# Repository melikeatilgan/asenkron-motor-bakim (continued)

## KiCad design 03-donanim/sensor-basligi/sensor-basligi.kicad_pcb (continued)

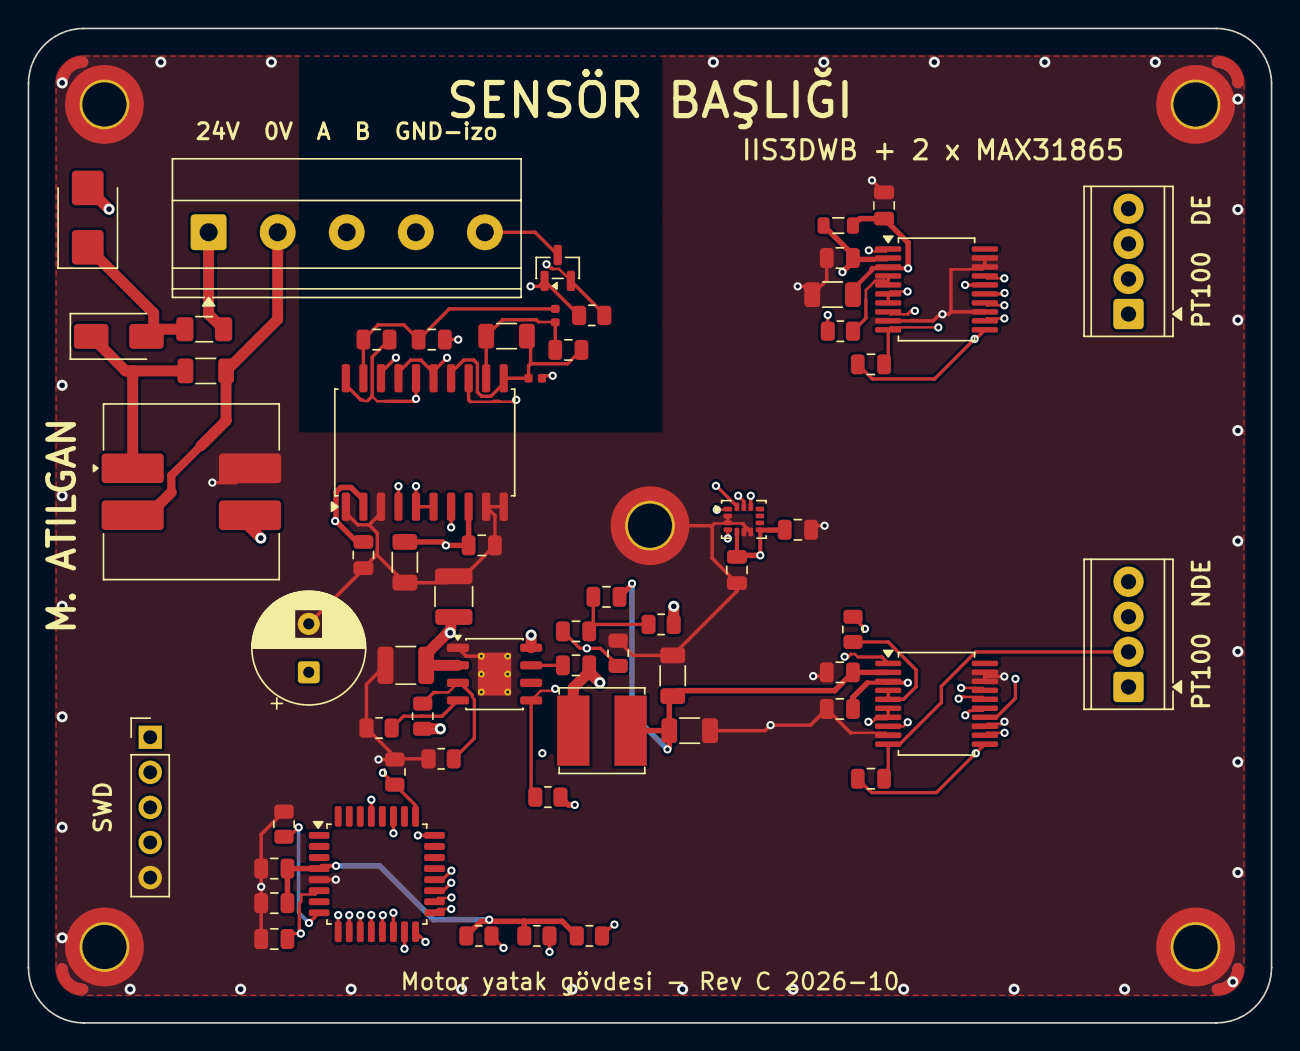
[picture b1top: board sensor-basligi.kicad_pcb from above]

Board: 4 copper layers, 90.0 x 72.0 mm, 66 parts (0 on the bottom side), 50 nets.

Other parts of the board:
MH1, MH2, MH3, MH4, MH5: MountingHole_3.2mm_M3_ISO7380_Pad_TopBottom

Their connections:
GND: MH1.1, MH2.1, MH3.1, MH4.1, MH5.1; also elsewhere on the board

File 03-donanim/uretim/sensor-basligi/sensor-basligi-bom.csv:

"Refs","Value","Footprint","Qty","DNP"
"C1","470n 100V","Capacitor_SMD:C_1206_3216Metric","1",""
"C2","2u2 100V","Capacitor_SMD:C_1210_3225Metric","1",""
"C3","2n2 50V","Capacitor_SMD:C_0805_2012Metric","1",""
"C4","22u 10V","Capacitor_SMD:C_1206_3216Metric","1",""
"C5","22u 10V","Capacitor_SMD:C_1206_3216Metric","1",""
"C6","3n3","Capacitor_SMD:C_0805_2012Metric","1",""
"C7","330p","Capacitor_SMD:C_0805_2012Metric","1",""
"C8","2u2 100V","Capacitor_SMD:C_1210_3225Metric","1",""
"C9","47u 63V","Capacitor_THT:CP_Radial_D8.0mm_P3.50mm","1",""
"C10","10u","Capacitor_SMD:C_1206_3216Metric","1",""
"C20","100n","Capacitor_SMD:C_0805_2012Metric","1",""
"C21","1u","Capacitor_SMD:C_0805_2012Metric","1",""
"C22","100n","Capacitor_SMD:C_0805_2012Metric","1",""
"C30","100n","Capacitor_SMD:C_0805_2012Metric","1",""
"C31","1u","Capacitor_SMD:C_0805_2012Metric","1",""
"C40","100n","Capacitor_SMD:C_0805_2012Metric","1",""
"C41","100n","Capacitor_SMD:C_0805_2012Metric","1",""
"C42","100n","Capacitor_SMD:C_0805_2012Metric","1",""
"C43","100n","Capacitor_SMD:C_0805_2012Metric","1",""
"C44","100n","Capacitor_SMD:C_0805_2012Metric","1",""
"C45","100n","Capacitor_SMD:C_0805_2012Metric","1",""
"C50","100n","Capacitor_SMD:C_0805_2012Metric","1",""
"C51","10u","Capacitor_SMD:C_1206_3216Metric","1",""
"C52","100n","Capacitor_SMD:C_0805_2012Metric","1",""
"C53","100n","Capacitor_SMD:C_0805_2012Metric","1",""
"C54","10u","Capacitor_SMD:C_1206_3216Metric","1",""
"C55","100n","Capacitor_SMD:C_0805_2012Metric","1",""
"C56","10n","Capacitor_SMD:C_0805_2012Metric","1",""
"D1","SMBJ33CA","Diode_SMD:D_SMB","1",""
"D2","SS110","Diode_SMD:D_SMA","1",""
"D10","SM712","Package_TO_SOT_SMD:SOT-23","1",""
"F1","500mA T 63V 0468.500NR","Fuse:Fuse_1206_3216Metric","1",""
"FB1","600R 100MHz","Inductor_SMD:L_0805_2012Metric","1",""
"FB2","BLM15HD182SN1D","Inductor_SMD:L_0402_1005Metric","1",""
"FB3","BLM15HD182SN1D","Inductor_SMD:L_0402_1005Metric","1",""
"J1","Ana karta kablo","TerminalBlock_Phoenix:TerminalBlock_Phoenix_MKDS-1,5-5_1x05_P5.00mm_Horizontal","1",""
"J2","PT100 4 telli","TerminalBlock_Phoenix:TerminalBlock_Phoenix_MPT-0,5-4-2.54_1x04_P2.54mm_Horizontal","1",""
"J3","PT100 4 telli","TerminalBlock_Phoenix:TerminalBlock_Phoenix_MPT-0,5-4-2.54_1x04_P2.54mm_Horizontal","1",""
"J4","SWD","Connector_PinHeader_2.54mm:PinHeader_1x05_P2.54mm_Vertical","1",""
"L1","SRF1260-101M","Inductor_SMD:L_CommonModeChoke_Bourns_SRF1260","1",""
"L2","33uH SRN6045TA-330M","Inductor_SMD:L_Bourns_SRN6045TA","1",""
"R1","499k","Resistor_SMD:R_0805_2012Metric","1",""
"R2","48k7","Resistor_SMD:R_0805_2012Metric","1",""
"R3","86k6","Resistor_SMD:R_0805_2012Metric","1",""
"R4","49k9","Resistor_SMD:R_0805_2012Metric","1",""
"R5","27k4","Resistor_SMD:R_0805_2012Metric","1",""
"R6","143k","Resistor_SMD:R_0805_2012Metric","1",""
"R10","10k","Resistor_SMD:R_0805_2012Metric","1",""
"R11","10k","Resistor_SMD:R_0805_2012Metric","1",""
"R12","10k","Resistor_SMD:R_0805_2012Metric","1",""
"R13","10k","Resistor_SMD:R_0805_2012Metric","1",""
"R14","10k","Resistor_SMD:R_0805_2012Metric","1",""
"R20","400R 0.1% 10ppm","Resistor_SMD:R_0805_2012Metric","1",""
"R21","400R 0.1% 10ppm","Resistor_SMD:R_0805_2012Metric","1",""
"R30","120R","Resistor_SMD:R_0805_2012Metric","1",""
"U1","LM5164DDA","Package_SO:HSOP-8-1EP_3.9x4.9mm_P1.27mm_EP2.41x3.1mm_ThermalVias","1",""
"U3","STM32G071KBTxN","Package_QFP:LQFP-32_7x7mm_P0.8mm","1",""
"U4","IIS3DWB","Package_LGA:LGA-14_3x2.5mm_P0.5mm_LayoutBorder3x4y","1",""
"U5","MAX31865AAP+","Package_SO:SSOP-20_5.3x7.2mm_P0.65mm","1",""
"U6","MAX31865AAP+","Package_SO:SSOP-20_5.3x7.2mm_P0.65mm","1",""
"U7","ADM2582E","Package_SO:SOIC-20W_7.5x12.8mm_P1.27mm","1",""

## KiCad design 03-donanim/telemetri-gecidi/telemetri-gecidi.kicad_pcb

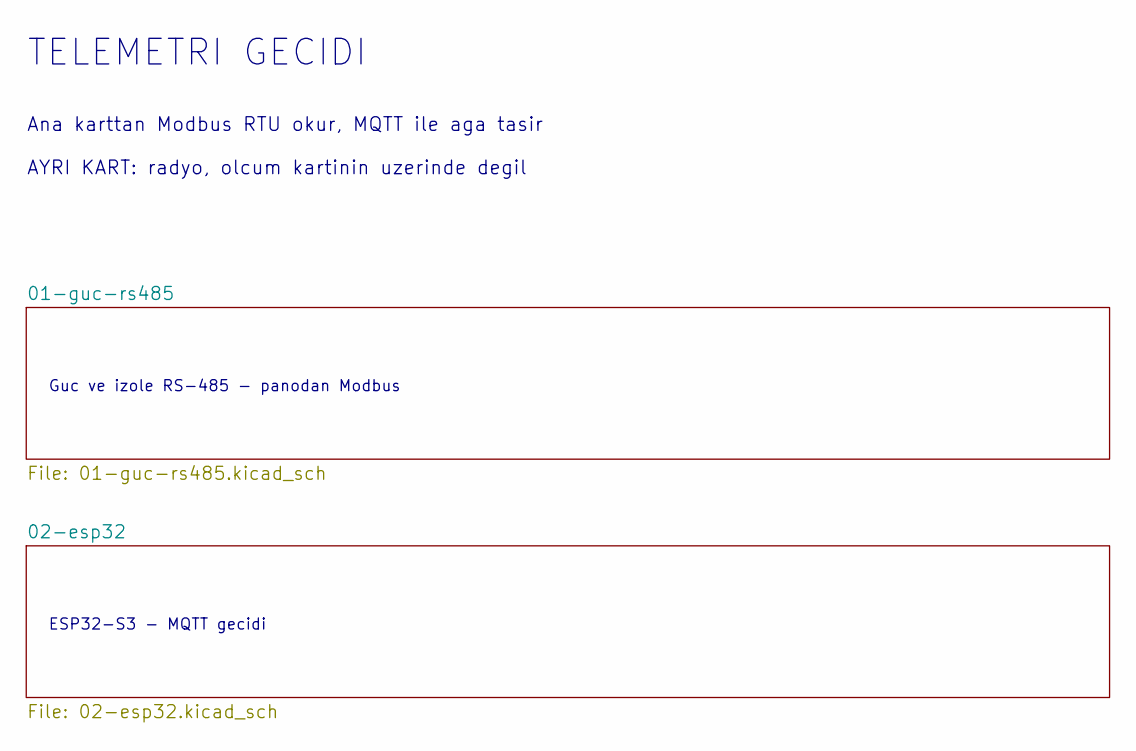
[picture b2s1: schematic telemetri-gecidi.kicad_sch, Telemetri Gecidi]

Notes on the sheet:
AYRI KART: radyo, olcum kartinin uzerinde degil
Ana karttan Modbus RTU okur, MQTT ile aga tasir
ESP32-S3 - MQTT gecidi
Guc ve izole RS-485 - panodan Modbus
TELEMETRI GECIDI

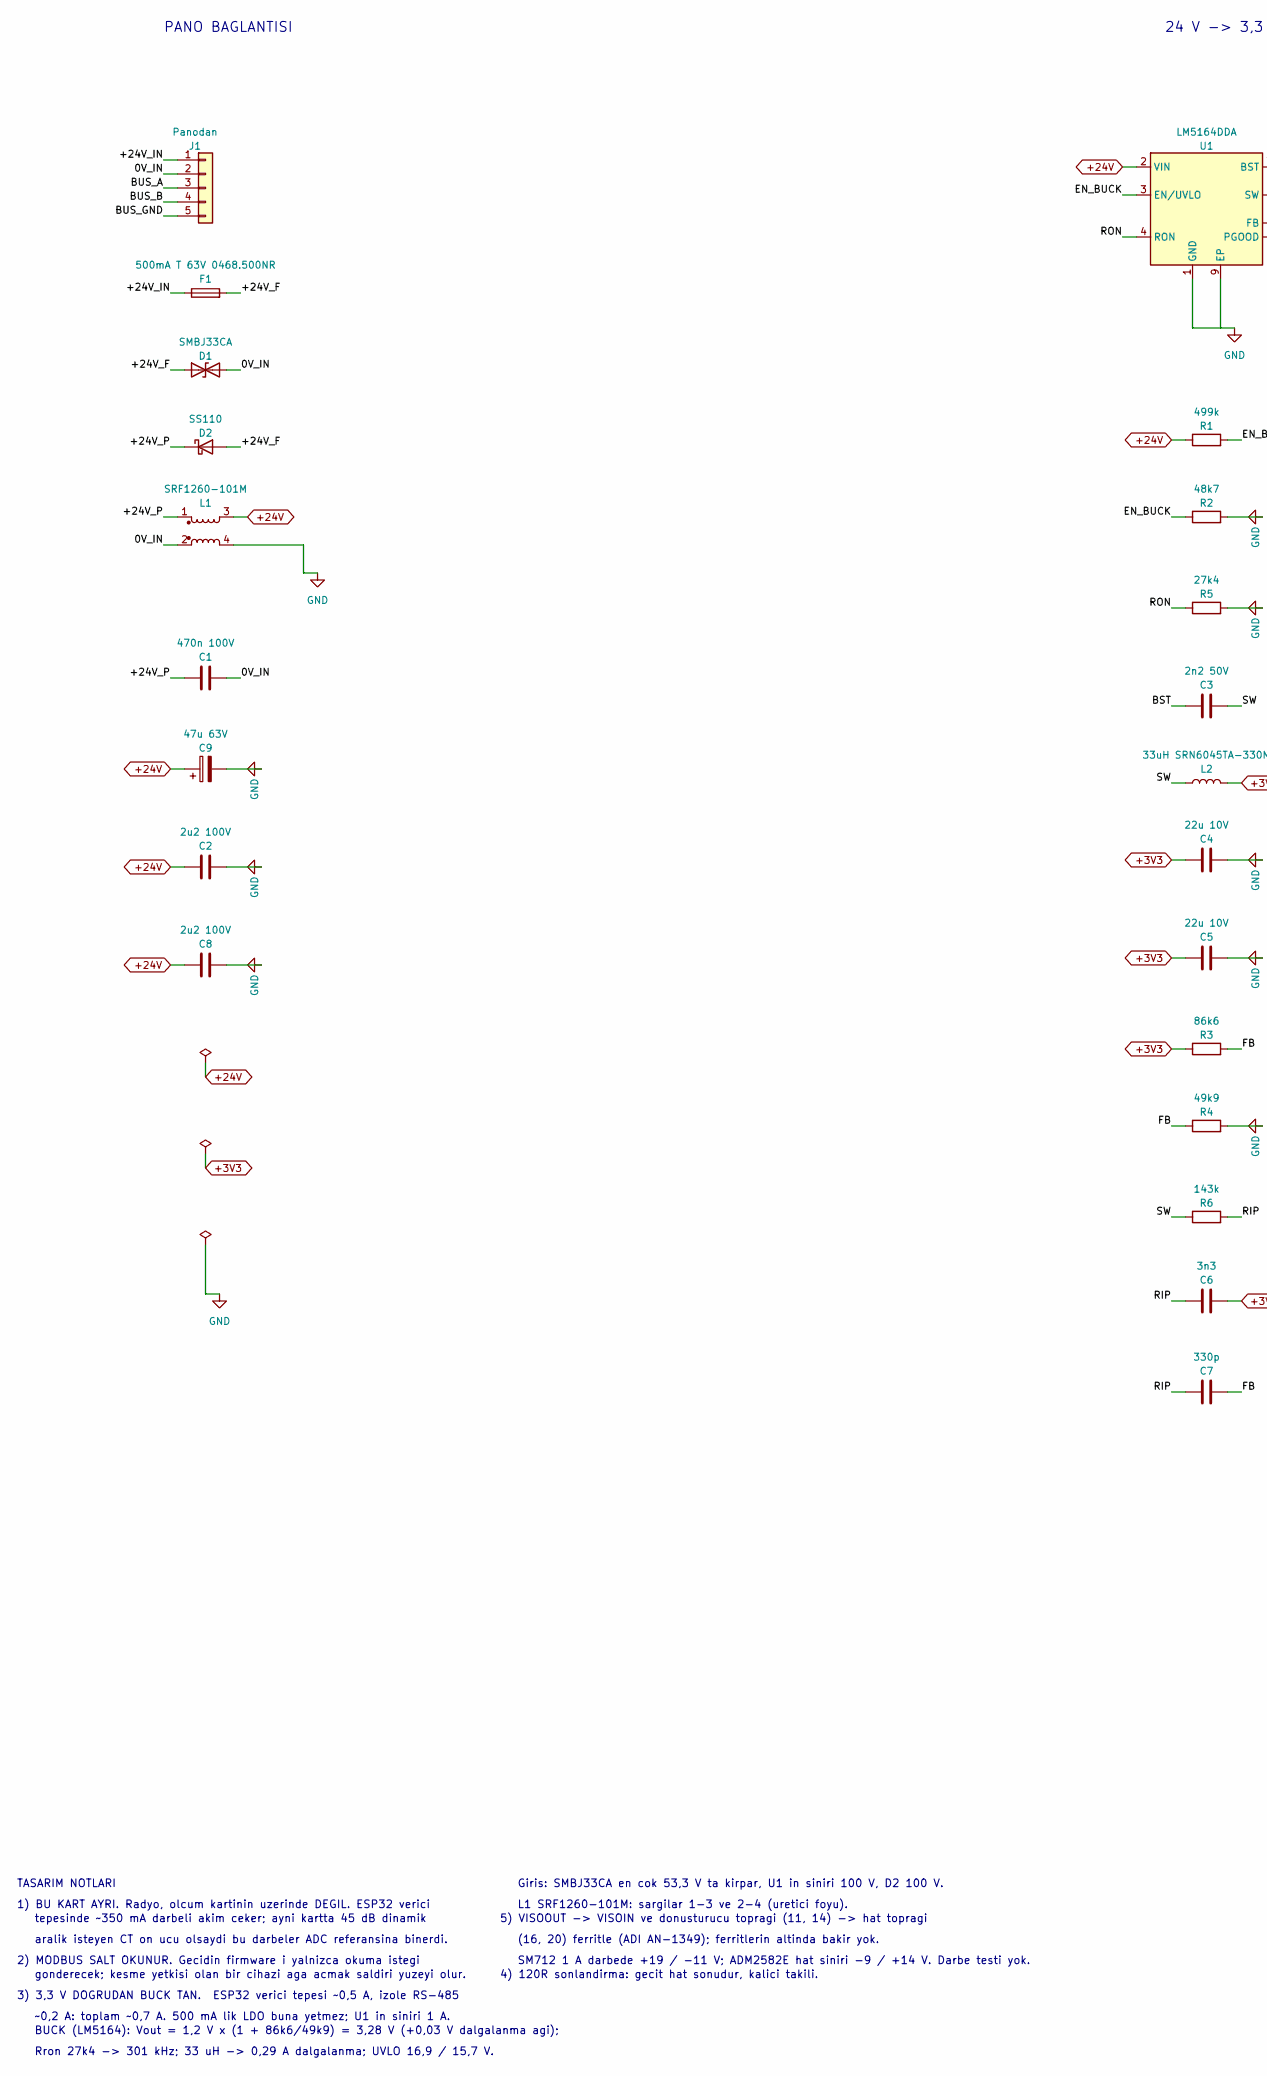
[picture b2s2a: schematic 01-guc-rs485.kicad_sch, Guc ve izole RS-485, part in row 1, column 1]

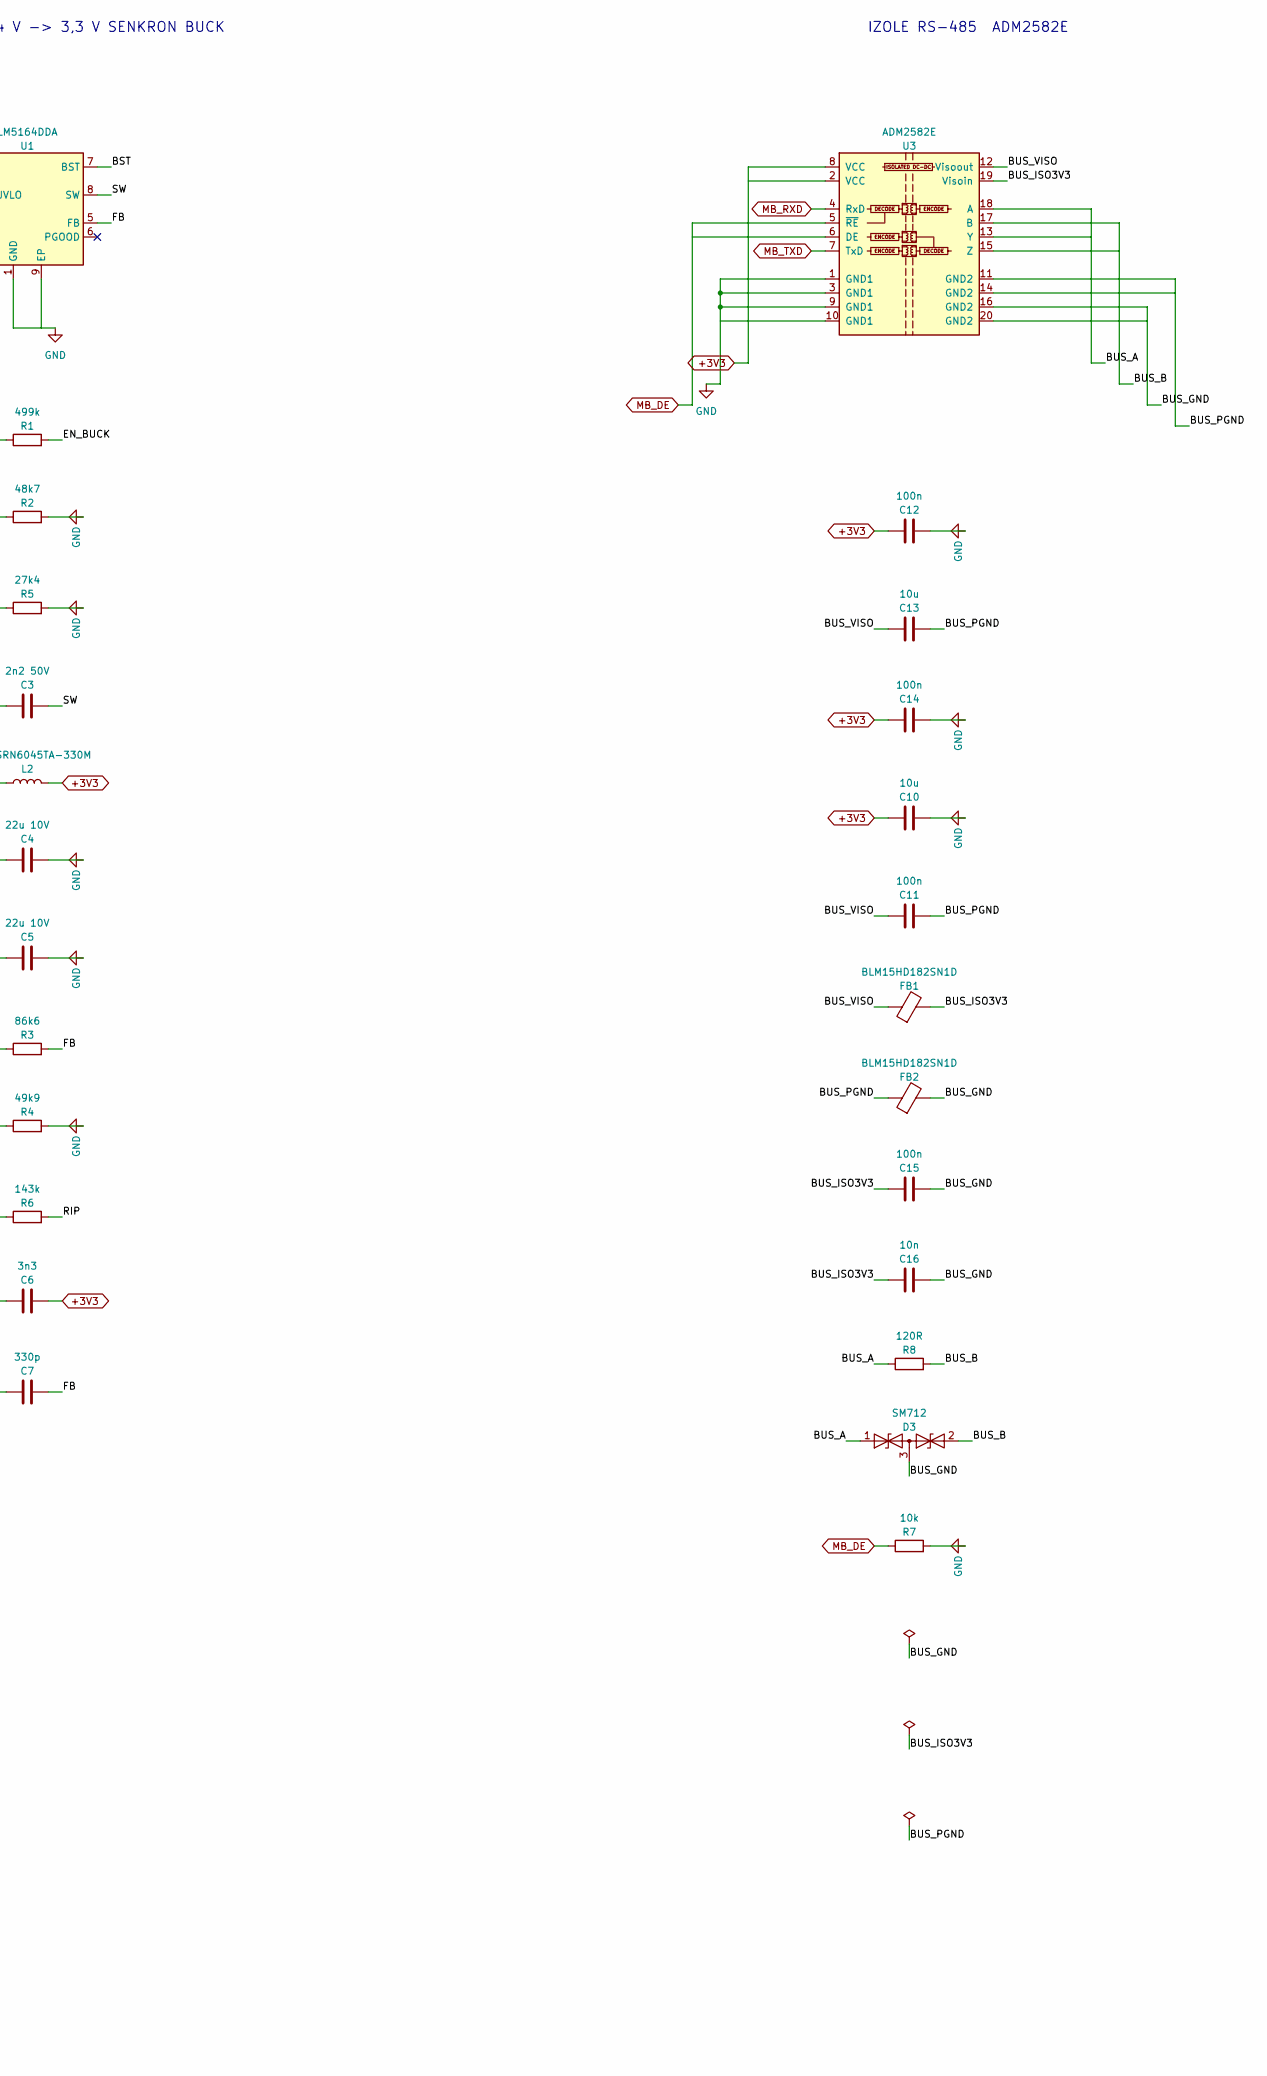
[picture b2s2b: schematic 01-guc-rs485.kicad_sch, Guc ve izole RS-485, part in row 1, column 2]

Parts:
C1: 470n 100V; C_1206_3216Metric
C2, C8: 2u2 100V; C_1210_3225Metric
C3: 2n2 50V; C_0805_2012Metric
C4, C5: 22u 10V; C_1206_3216Metric
C6: 3n3; C_0805_2012Metric
C7: 330p; C_0805_2012Metric
C9: 47u 63V; CP_Radial_D8.0mm_P3.50mm
C10, C13: 10u; C_1206_3216Metric
C11, C12, C14, C15: 100n; C_0805_2012Metric
C16: 10n; C_0805_2012Metric
D1: SMBJ33CA; D_SMB
D2: SS110; D_SMA
D3: SM712; SOT-23
F1: 500mA T 63V 0468.500NR; Fuse_1206_3216Metric
FB1, FB2: BLM15HD182SN1D; L_0402_1005Metric
J1: Panodan; TerminalBlock_Phoenix_MKDS-1,5-5_1x05_P5.00mm_Horizontal
L1: SRF1260-101M; L_CommonModeChoke_Bourns_SRF1260
L2: 33uH SRN6045TA-330M; L_Bourns_SRN6045TA
R1: 499k; R_0805_2012Metric
R2: 48k7; R_0805_2012Metric
R3: 86k6; R_0805_2012Metric
R4: 49k9; R_0805_2012Metric
R5: 27k4; R_0805_2012Metric
R6: 143k; R_0805_2012Metric
R7: 10k; R_0805_2012Metric
R8: 120R; R_0805_2012Metric
U1: LM5164DDA; HSOP-8-1EP_3.9x4.9mm_P1.27mm_EP2.41x3.1mm_ThermalVias
U3: ADM2582E; SOIC-20W_7.5x12.8mm_P1.27mm

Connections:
+3V3: C4.1, C5.1, C6.2, C10.1, C12.1, C14.1, L2.2, R3.1, U3.2 (VCC), U3.8 (VCC); also elsewhere on the board
+24V: C2.1, C8.1, C9.1, L1.3, R1.1, U1.2 (VIN)
/01-guc-rs485/0V_IN: C1.2, D1.2 (A2), J1.2, L1.2
/01-guc-rs485/+24V_F: D1.1 (A1), D2.2 (A), F1.2
/01-guc-rs485/+24V_IN: F1.1, J1.1
/01-guc-rs485/+24V_P: C1.1, D2.1 (K), L1.1
/01-guc-rs485/BST: C3.1, U1.7 (BST)
/01-guc-rs485/BUS_A: D3.1 (A1), J1.3, R8.1, U3.13 (Y), U3.18 (A)
/01-guc-rs485/BUS_B: D3.2 (A2), J1.4, R8.2, U3.15 (Z), U3.17 (B)
/01-guc-rs485/BUS_GND: C15.2, C16.2, D3.3 (common), FB2.2, J1.5, U3.16 (GND2), U3.20 (GND2)
/01-guc-rs485/BUS_ISO3V3: C15.1, C16.1, FB1.2, U3.19 (Visoin)
/01-guc-rs485/BUS_PGND: C11.2, C13.2, FB2.1, U3.11 (GND2), U3.14 (GND2)
/01-guc-rs485/BUS_VISO: C11.1, C13.1, FB1.1, U3.12 (Visoout)
/01-guc-rs485/EN_BUCK: R1.2, R2.1, U1.3 (EN/UVLO)
/01-guc-rs485/FB: C7.2, R3.2, R4.1, U1.5 (FB)
/01-guc-rs485/RIP: C6.1, C7.1, R6.2
/01-guc-rs485/RON: R5.1, U1.4 (RON)
/01-guc-rs485/SW: C3.2, L2.1, R6.1, U1.8 (SW)
GND: C2.2, C4.2, C5.2, C8.2, C9.2, C10.2, C12.2, C14.2, L1.4, R2.2, R4.2, R5.2, R7.2, U1.1 (GND), U1.9 (EP), U3.1 (GND1), U3.3 (GND1), U3.9 (GND1), U3.10 (GND1); also elsewhere on the board
MB_DE: R7.1, U3.5 (~RE), U3.6 (DE); also elsewhere on the board
MB_RXD: U3.4 (RxD); also elsewhere on the board
MB_TXD: U3.7 (TxD); also elsewhere on the board

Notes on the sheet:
tepesinde ~350 mA darbeli akim ceker; ayni kartta 45 dB dinamik
24 V -> 3,3 V SENKRON BUCK
Giris: SMBJ33CA en cok 53,3 V ta kirpar, U1 in siniri 100 V, D2 100 V.
BUCK (LM5164): Vout = 1,2 V x (1 + 86k6/49k9) = 3,28 V (+0,03 V dalgalanma agi);
SM712 1 A darbede +19 / -11 V; ADM2582E hat siniri -9 / +14 V. Darbe testi yok.
aralik isteyen CT on ucu olsaydi bu darbeler ADC referansina binerdi.
TASARIM NOTLARI
gonderecek; kesme yetkisi olan bir cihazi aga acmak saldiri yuzeyi olur.
IZOLE RS-485 ADM2582E
Rron 27k4 -> 301 kHz; 33 uH -> 0,29 A dalgalanma; UVLO 16,9 / 15,7 V.
5) VISOOUT -> VISOIN ve donusturucu topragi (11, 14) -> hat topragi
1) BU KART AYRI. Radyo, olcum kartinin uzerinde DEGIL. ESP32 verici
L1 SRF1260-101M: sargilar 1-3 ve 2-4 (uretici foyu).
2) MODBUS SALT OKUNUR. Gecidin firmware i yalnizca okuma istegi
(16, 20) ferritle (ADI AN-1349); ferritlerin altinda bakir yok.
PANO BAGLANTISI
3) 3,3 V DOGRUDAN BUCK TAN. ESP32 verici tepesi ~0,5 A, izole RS-485
4) 120R sonlandirma: gecit hat sonudur, kalici takili.
~0,2 A: toplam ~0,7 A. 500 mA lik LDO buna yetmez; U1 in siniri 1 A.

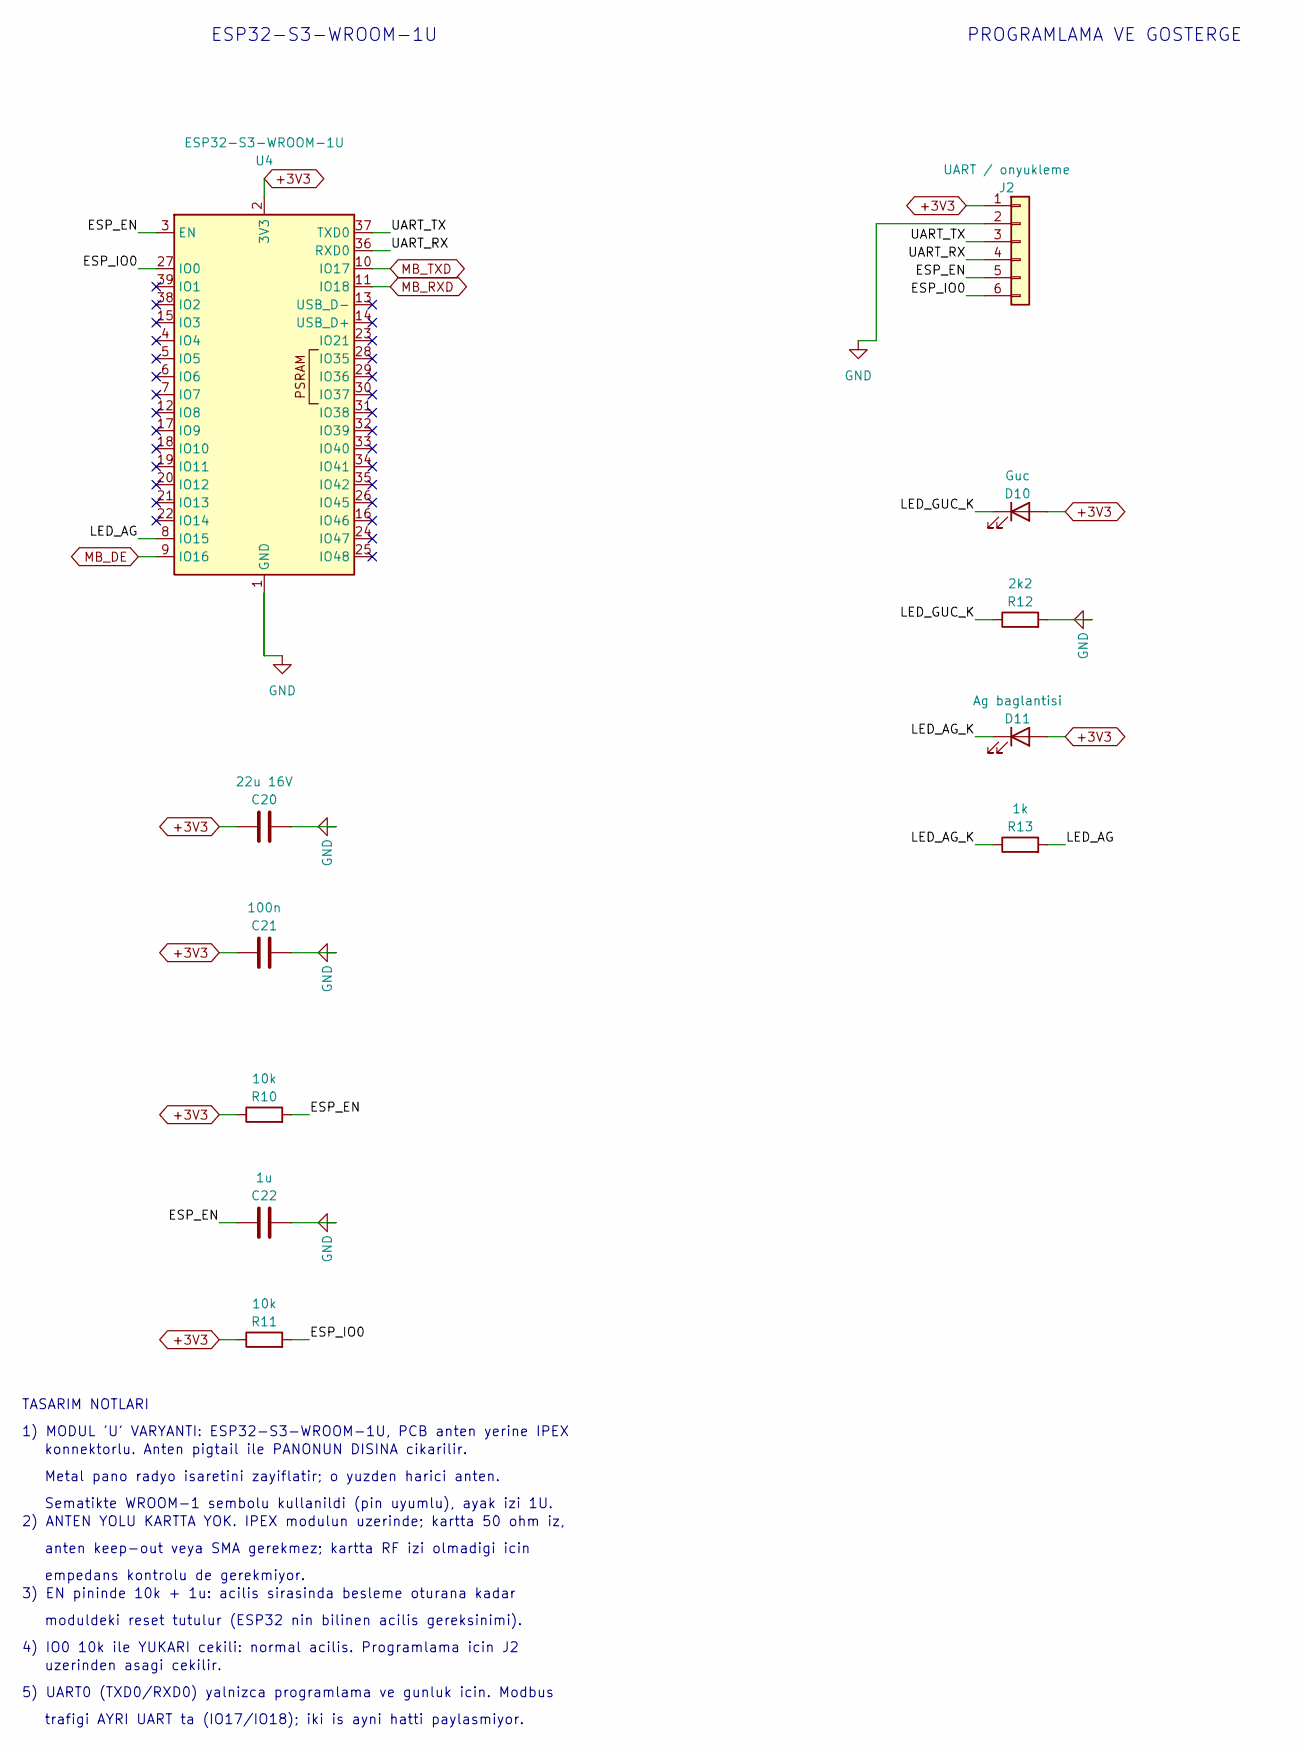
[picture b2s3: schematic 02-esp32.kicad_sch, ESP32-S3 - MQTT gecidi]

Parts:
C20: 22u 16V; C_1206_3216Metric
C21: 100n; C_0805_2012Metric
C22: 1u; C_0805_2012Metric
D10: Guc; LED_0805_2012Metric
D11: Ag baglantisi; LED_0805_2012Metric
J2: UART / onyukleme; PinHeader_1x06_P2.54mm_Vertical
R10, R11: 10k; R_0805_2012Metric
R12: 2k2; R_0805_2012Metric
R13: 1k; R_0805_2012Metric
U4: ESP32-S3-WROOM-1U

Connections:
+3V3: C20.1, C21.1, D10.2 (A), D11.2 (A), J2.1, R10.1, R11.1, U4.2 (3V3); also elsewhere on the board
/02-esp32/ESP_EN: C22.1, J2.5, R10.2, U4.3 (EN)
/02-esp32/ESP_IO0: J2.6, R11.2, U4.27 (IO0)
/02-esp32/LED_AG: R13.2, U4.8 (IO15)
/02-esp32/LED_AG_K: D11.1 (K), R13.1
/02-esp32/LED_GUC_K: D10.1 (K), R12.1
/02-esp32/UART_RX: J2.4, U4.36 (RXD0)
/02-esp32/UART_TX: J2.3, U4.37 (TXD0)
GND: C20.2, C21.2, C22.2, J2.2, R12.2, U4.1 (GND), U4.40 (GND), U4.41 (GND); also elsewhere on the board
MB_DE: U4.9 (IO16); also elsewhere on the board
MB_RXD: U4.11 (IO18); also elsewhere on the board
MB_TXD: U4.10 (IO17); also elsewhere on the board

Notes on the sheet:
empedans kontrolu de gerekmiyor.
1) MODUL 'U' VARYANTI: ESP32-S3-WROOM-1U, PCB anten yerine IPEX
PROGRAMLAMA VE GOSTERGE
trafigi AYRI UART ta (IO17/IO18); iki is ayni hatti paylasmiyor.
3) EN pininde 10k + 1u: acilis sirasinda besleme oturana kadar
konnektorlu. Anten pigtail ile PANONUN DISINA cikarilir.
TASARIM NOTLARI
moduldeki reset tutulur (ESP32 nin bilinen acilis gereksinimi).
Metal pano radyo isaretini zayiflatir; o yuzden harici anten.
2) ANTEN YOLU KARTTA YOK. IPEX modulun uzerinde; kartta 50 ohm iz,
4) IO0 10k ile YUKARI cekili: normal acilis. Programlama icin J2
5) UART0 (TXD0/RXD0) yalnizca programlama ve gunluk icin. Modbus
anten keep-out veya SMA gerekmez; kartta RF izi olmadigi icin
ESP32-S3-WROOM-1U
Sematikte WROOM-1 sembolu kullanildi (pin uyumlu), ayak izi 1U.
uzerinden asagi cekilir.

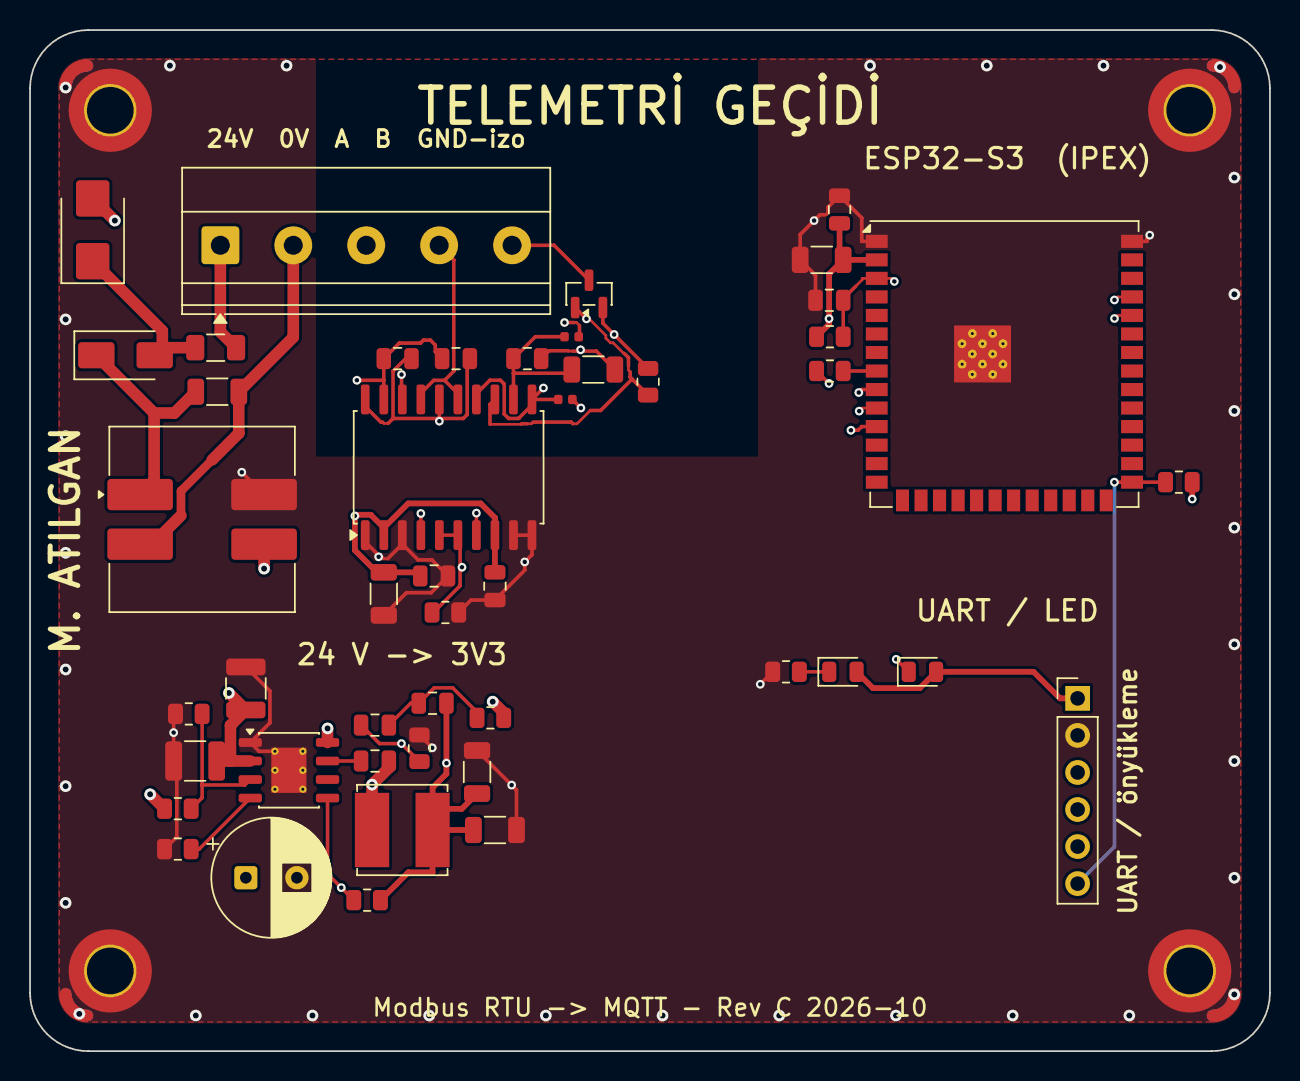
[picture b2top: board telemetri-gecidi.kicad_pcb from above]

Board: 4 copper layers, 85.0 x 70.0 mm, 50 parts (0 on the bottom side), 29 nets.

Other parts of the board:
MH1, MH2, MH3, MH4: MountingHole_3.2mm_M3_ISO7380_Pad_TopBottom

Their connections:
GND: MH1.1, MH2.1, MH3.1, MH4.1; also elsewhere on the board

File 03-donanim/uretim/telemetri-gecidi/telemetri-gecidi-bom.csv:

"Refs","Value","Footprint","Qty","DNP"
"C1","470n 100V","Capacitor_SMD:C_1206_3216Metric","1",""
"C2","2u2 100V","Capacitor_SMD:C_1210_3225Metric","1",""
"C3","2n2 50V","Capacitor_SMD:C_0805_2012Metric","1",""
"C4","22u 10V","Capacitor_SMD:C_1206_3216Metric","1",""
"C5","22u 10V","Capacitor_SMD:C_1206_3216Metric","1",""
"C6","3n3","Capacitor_SMD:C_0805_2012Metric","1",""
"C7","330p","Capacitor_SMD:C_0805_2012Metric","1",""
"C8","2u2 100V","Capacitor_SMD:C_1210_3225Metric","1",""
"C9","47u 63V","Capacitor_THT:CP_Radial_D8.0mm_P3.50mm","1",""
"C10","10u","Capacitor_SMD:C_1206_3216Metric","1",""
"C11","100n","Capacitor_SMD:C_0805_2012Metric","1",""
"C12","100n","Capacitor_SMD:C_0805_2012Metric","1",""
"C13","10u","Capacitor_SMD:C_1206_3216Metric","1",""
"C14","100n","Capacitor_SMD:C_0805_2012Metric","1",""
"C15","100n","Capacitor_SMD:C_0805_2012Metric","1",""
"C16","10n","Capacitor_SMD:C_0805_2012Metric","1",""
"C20","22u 16V","Capacitor_SMD:C_1206_3216Metric","1",""
"C21","100n","Capacitor_SMD:C_0805_2012Metric","1",""
"C22","1u","Capacitor_SMD:C_0805_2012Metric","1",""
"D1","SMBJ33CA","Diode_SMD:D_SMB","1",""
"D2","SS110","Diode_SMD:D_SMA","1",""
"D3","SM712","Package_TO_SOT_SMD:SOT-23","1",""
"D10","Guc","LED_SMD:LED_0805_2012Metric","1",""
"D11","Ag baglantisi","LED_SMD:LED_0805_2012Metric","1",""
"F1","500mA T 63V 0468.500NR","Fuse:Fuse_1206_3216Metric","1",""
"FB1","BLM15HD182SN1D","Inductor_SMD:L_0402_1005Metric","1",""
"FB2","BLM15HD182SN1D","Inductor_SMD:L_0402_1005Metric","1",""
"J1","Panodan","TerminalBlock_Phoenix:TerminalBlock_Phoenix_MKDS-1,5-5_1x05_P5.00mm_Horizontal","1",""
"J2","UART / onyukleme","Connector_PinHeader_2.54mm:PinHeader_1x06_P2.54mm_Vertical","1",""
"L1","SRF1260-101M","Inductor_SMD:L_CommonModeChoke_Bourns_SRF1260","1",""
"L2","33uH SRN6045TA-330M","Inductor_SMD:L_Bourns_SRN6045TA","1",""
"R1","499k","Resistor_SMD:R_0805_2012Metric","1",""
"R2","48k7","Resistor_SMD:R_0805_2012Metric","1",""
"R3","86k6","Resistor_SMD:R_0805_2012Metric","1",""
"R4","49k9","Resistor_SMD:R_0805_2012Metric","1",""
"R5","27k4","Resistor_SMD:R_0805_2012Metric","1",""
"R6","143k","Resistor_SMD:R_0805_2012Metric","1",""
"R7","10k","Resistor_SMD:R_0805_2012Metric","1",""
"R8","120R","Resistor_SMD:R_0805_2012Metric","1",""
"R10","10k","Resistor_SMD:R_0805_2012Metric","1",""
"R11","10k","Resistor_SMD:R_0805_2012Metric","1",""
"R12","2k2","Resistor_SMD:R_0805_2012Metric","1",""
"R13","1k","Resistor_SMD:R_0805_2012Metric","1",""
"U1","LM5164DDA","Package_SO:HSOP-8-1EP_3.9x4.9mm_P1.27mm_EP2.41x3.1mm_ThermalVias","1",""
"U3","ADM2582E","Package_SO:SOIC-20W_7.5x12.8mm_P1.27mm","1",""
"U4","ESP32-S3-WROOM-1U","RF_Module:ESP32-S3-WROOM-1U","1",""

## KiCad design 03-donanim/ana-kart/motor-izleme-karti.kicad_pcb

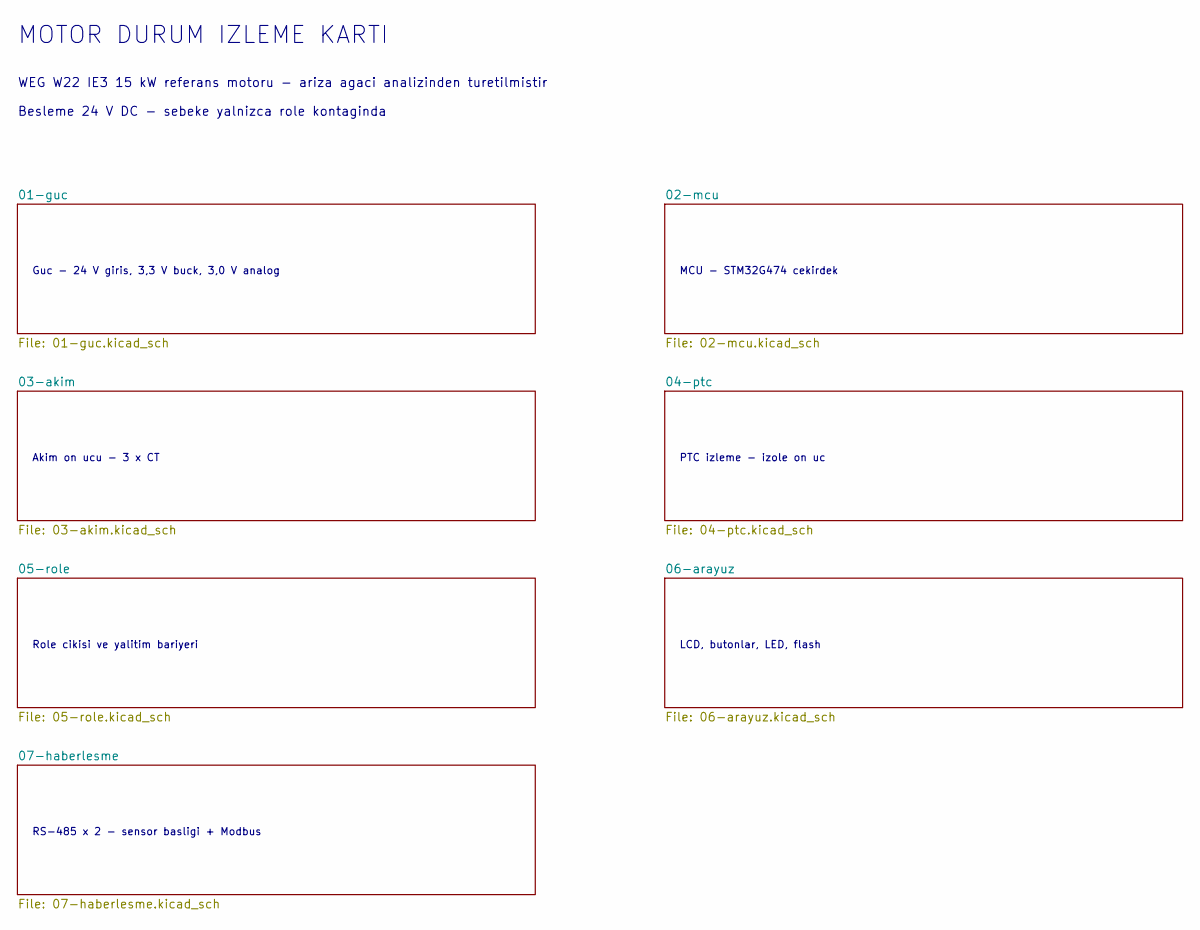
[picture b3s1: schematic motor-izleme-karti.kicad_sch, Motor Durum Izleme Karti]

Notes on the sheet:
MCU - STM32G474 cekirdek
Guc - 24 V giris, 3,3 V buck, 3,0 V analog
LCD, butonlar, LED, flash
Akim on ucu - 3 x CT
MOTOR DURUM IZLEME KARTI
PTC izleme - izole on uc
Besleme 24 V DC - sebeke yalnizca role kontaginda
WEG W22 IE3 15 kW referans motoru - ariza agaci analizinden turetilmistir
RS-485 x 2 - sensor basligi + Modbus
Role cikisi ve yalitim bariyeri
